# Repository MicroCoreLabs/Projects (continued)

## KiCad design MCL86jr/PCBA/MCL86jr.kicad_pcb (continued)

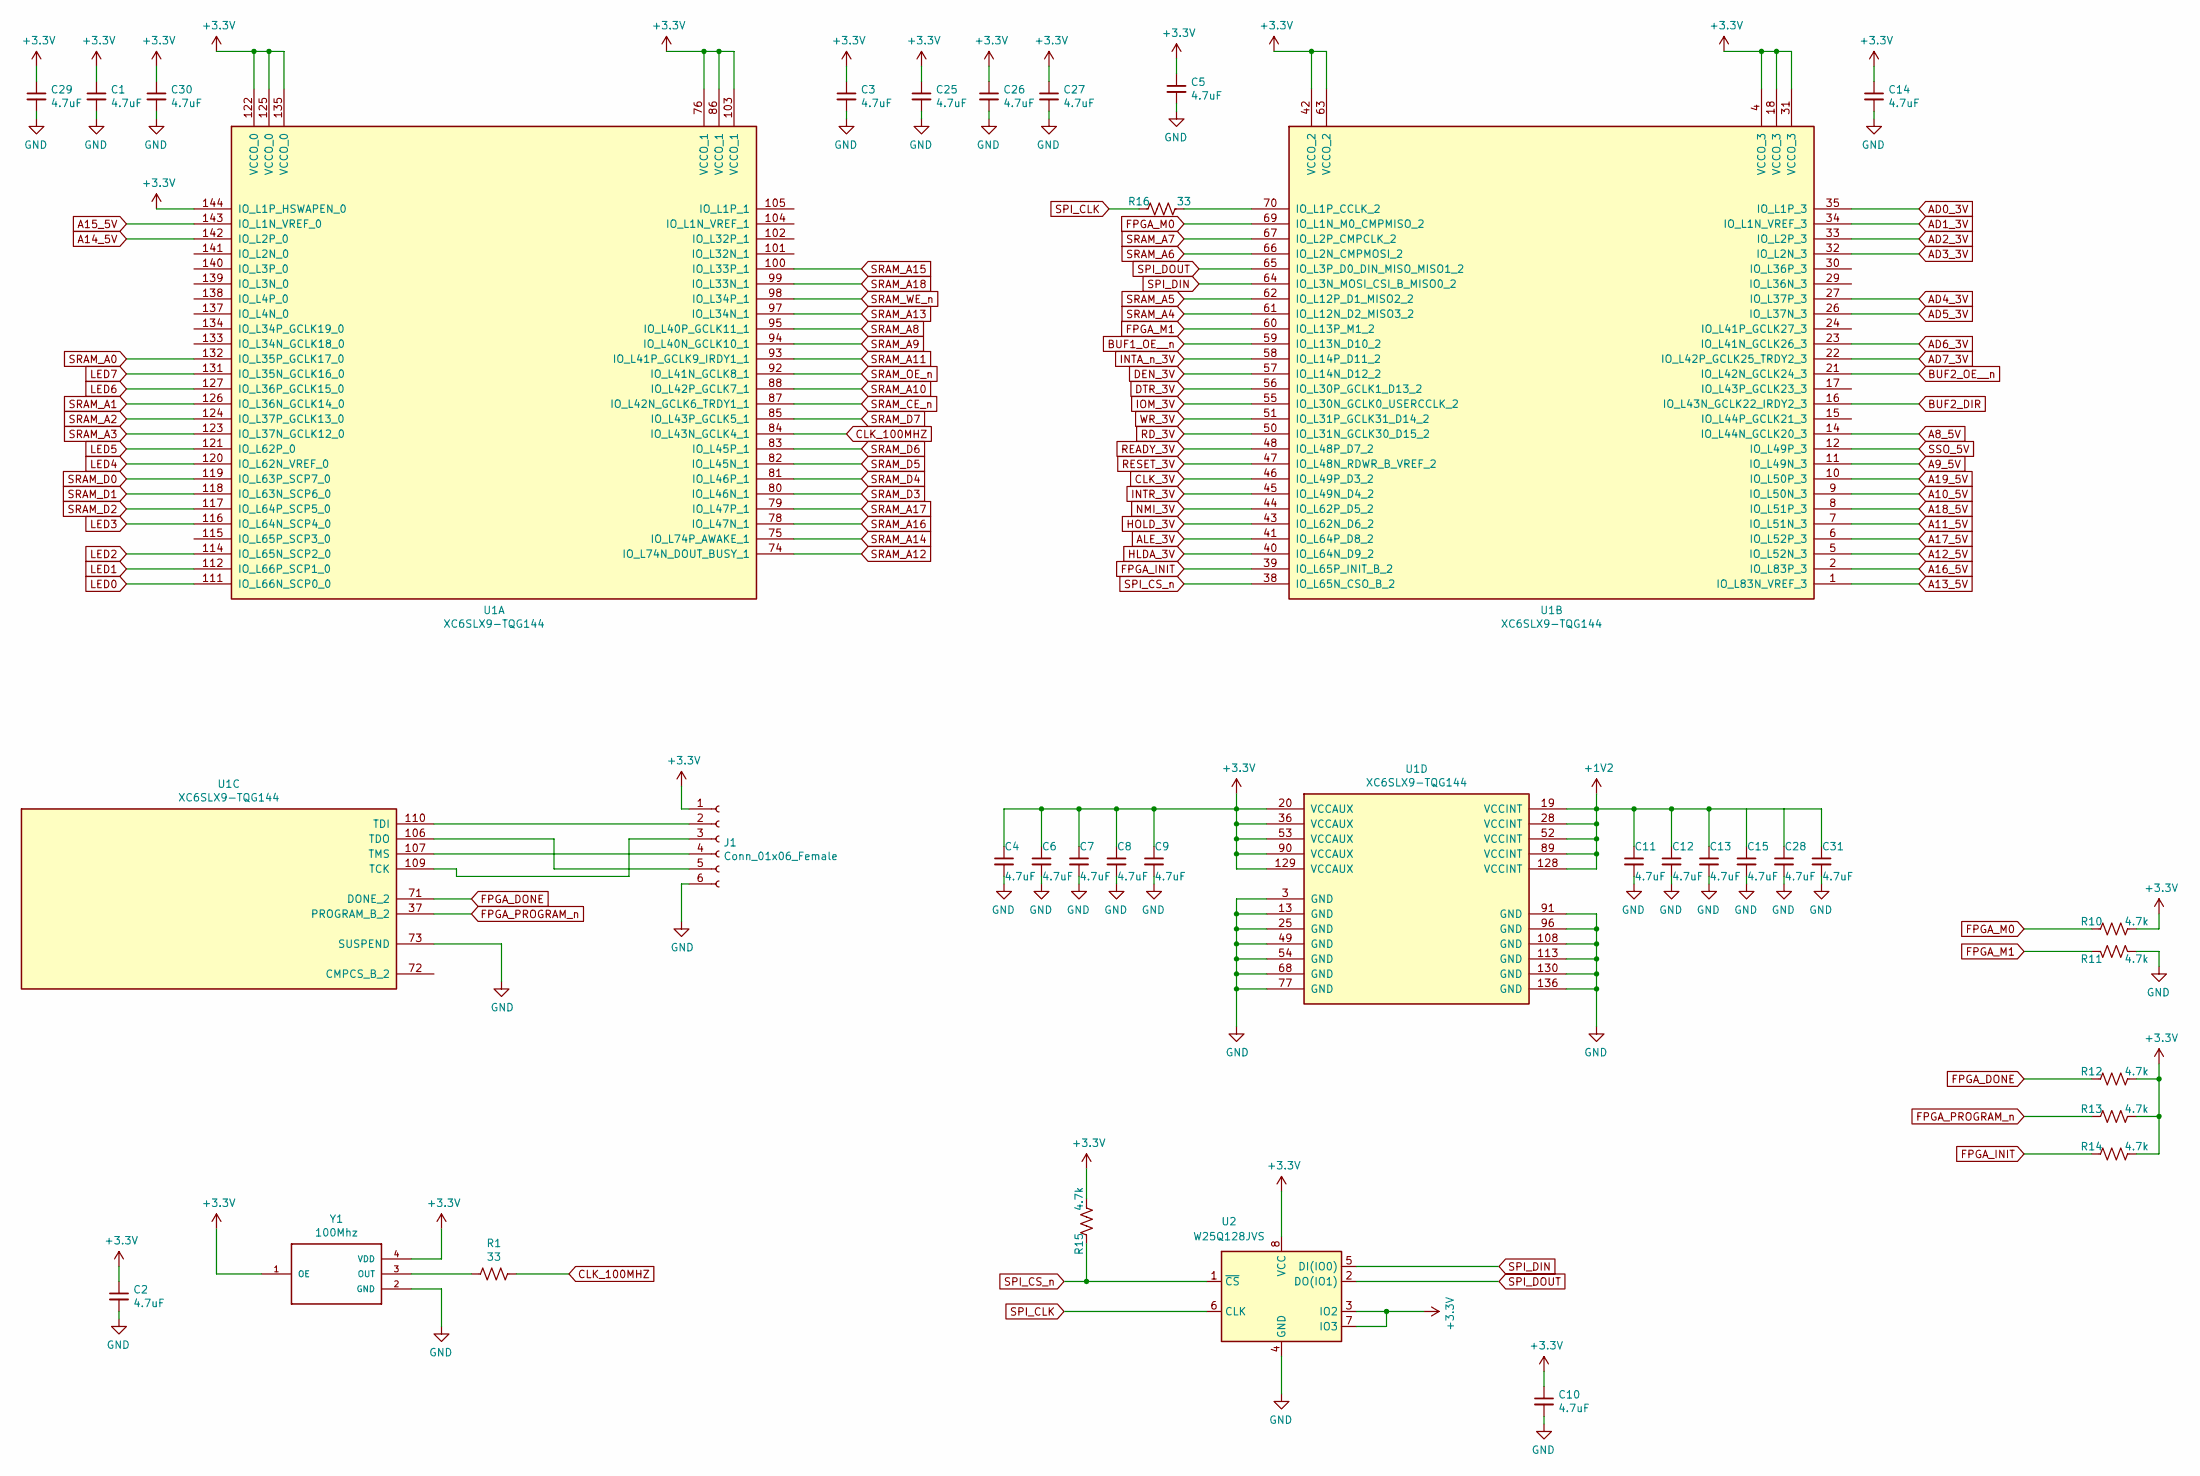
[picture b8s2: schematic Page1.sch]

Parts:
C1, C2, C3, C4, C5, C6, C7, C8, C9, C10, C11, C12, C13, C14, C15, C25, C26, C27, C28, C29, C30, C31: 4.7uF; C_0402_1005Metric
J1: Conn_01x06_Female; PinHeader_1x06_P2.54mm_Vertical
R1, R16: 33; R_0402_1005Metric
R10, R11, R12, R13, R14, R15: 4.7k; R_0402_1005Metric
U1: XC6SLX9-TQG144; TQFP-144_20x20mm_P0.5mm
U2: W25Q128JVS; SOIC-8_5.23x5.23mm_P1.27mm
Y1: 100Mhz; OSC_SIT8008BI-13-33E-33.333330E

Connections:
+1V2: C11.1, C12.1, C13.1, C15.1, C28.1, C31.1, U1.19 (VCCINT), U1.28 (VCCINT), U1.52 (VCCINT), U1.89 (VCCINT), U1.128 (VCCINT); also elsewhere on the board
+3V3: C1.1, C2.1, C3.1, C4.1, C5.1, C6.1, C7.1, C8.1, C9.1, C10.1, C14.1, C25.1, C26.1, C27.1, C29.1, C30.1, J1.1, R10.1, R12.1, R13.1, R14.1, R15.1, U1.4 (VCCO_3), U1.18 (VCCO_3), U1.20 (VCCAUX), U1.31 (VCCO_3), U1.36 (VCCAUX), U1.42 (VCCO_2), U1.53 (VCCAUX), U1.63 (VCCO_2), U1.76 (VCCO_1), U1.86 (VCCO_1), U1.90 (VCCAUX), U1.103 (VCCO_1), U1.122 (VCCO_0), U1.125 (VCCO_0), U1.129 (VCCAUX), U1.135 (VCCO_0), U1.144 (IO_L1P_HSWAPEN_0), U2.3 (IO2), U2.7 (IO3), U2.8 (VCC), Y1.1 (OE), Y1.4 (VDD); also elsewhere on the board
A8_5V: U1.14 (IO_L44N_GCLK20_3); also elsewhere on the board
A9_5V: U1.11 (IO_L49N_3); also elsewhere on the board
A10_5V: U1.9 (IO_L50N_3); also elsewhere on the board
A11_5V: U1.7 (IO_L51N_3); also elsewhere on the board
A12_5V: U1.5 (IO_L52N_3); also elsewhere on the board
A13_5V: U1.1 (IO_L83N_VREF_3); also elsewhere on the board
A14_5V: U1.142 (IO_L2P_0); also elsewhere on the board
A15_5V: U1.143 (IO_L1N_VREF_0); also elsewhere on the board
A16_5V: U1.2 (IO_L83P_3); also elsewhere on the board
A17_5V: U1.6 (IO_L52P_3); also elsewhere on the board
A18_5V: U1.8 (IO_L51P_3); also elsewhere on the board
A19_5V: U1.10 (IO_L50P_3); also elsewhere on the board
AD0_3V: U1.35 (IO_L1P_3); also elsewhere on the board
AD1_3V: U1.34 (IO_L1N_VREF_3); also elsewhere on the board
AD2_3V: U1.33 (IO_L2P_3); also elsewhere on the board
AD3_3V: U1.32 (IO_L2N_3); also elsewhere on the board
AD4_3V: U1.27 (IO_L37P_3); also elsewhere on the board
AD5_3V: U1.26 (IO_L37N_3); also elsewhere on the board
AD6_3V: U1.23 (IO_L41N_GCLK26_3); also elsewhere on the board
AD7_3V: U1.22 (IO_L42P_GCLK25_TRDY2_3); also elsewhere on the board
ALE_3V: U1.41 (IO_L64P_D8_2); also elsewhere on the board
BUF1_OE__n: U1.59 (IO_L13N_D10_2); also elsewhere on the board
BUF2_DIR: U1.16 (IO_L43N_GCLK22_IRDY2_3); also elsewhere on the board
BUF2_OE__n: U1.21 (IO_L42N_GCLK24_3); also elsewhere on the board
CLK_3V: U1.46 (IO_L49P_D3_2); also elsewhere on the board
CLK_100MHZ: R1.1, U1.84 (IO_L43N_GCLK4_1)
DEN_3V: U1.57 (IO_L14N_D12_2); also elsewhere on the board
DTR_3V: U1.56 (IO_L30P_GCLK1_D13_2); also elsewhere on the board
FPGA_DONE: R12.2, U1.71 (DONE_2)
FPGA_INIT: R14.2, U1.39 (IO_L65P_INIT_B_2)
FPGA_M0: R10.2, U1.69 (IO_L1N_M0_CMPMISO_2)
FPGA_M1: R11.2, U1.60 (IO_L13P_M1_2)
FPGA_PROGRAM_n: R13.2, U1.37 (PROGRAM_B_2)
GND: C1.2, C2.2, C3.2, C4.2, C5.2, C6.2, C7.2, C8.2, C9.2, C10.2, C11.2, C12.2, C13.2, C14.2, C15.2, C25.2, C26.2, C27.2, C28.2, C29.2, C30.2, C31.2, J1.6, R11.1, U1.3 (GND), U1.13 (GND), U1.25 (GND), U1.49 (GND), U1.54 (GND), U1.68 (GND), U1.73 (SUSPEND), U1.77 (GND), U1.91 (GND), U1.96 (GND), U1.108 (GND), U1.113 (GND), U1.130 (GND), U1.136 (GND), U2.4 (GND), Y1.2 (GND); also elsewhere on the board
HLDA_3V: U1.40 (IO_L64N_D9_2); also elsewhere on the board
HOLD_3V: U1.43 (IO_L62N_D6_2); also elsewhere on the board
INTA_n_3V: U1.58 (IO_L14P_D11_2); also elsewhere on the board
INTR_3V: U1.45 (IO_L49N_D4_2); also elsewhere on the board
IOM_3V: U1.55 (IO_L30N_GCLK0_USERCCLK_2); also elsewhere on the board
LED0: U1.111 (IO_L66N_SCP0_0); also elsewhere on the board
LED1: U1.112 (IO_L66P_SCP1_0); also elsewhere on the board
LED2: U1.114 (IO_L65N_SCP2_0); also elsewhere on the board
LED3: U1.116 (IO_L64N_SCP4_0); also elsewhere on the board
LED4: U1.120 (IO_L62N_VREF_0); also elsewhere on the board
LED5: U1.121 (IO_L62P_0); also elsewhere on the board
LED6: U1.127 (IO_L36P_GCLK15_0); also elsewhere on the board
LED7: U1.131 (IO_L35N_GCLK16_0); also elsewhere on the board
NMI_3V: U1.44 (IO_L62P_D5_2); also elsewhere on the board
unnamed: J1.2, U1.110 (TDI)
unnamed: J1.3, U1.109 (TCK)
unnamed: J1.4, U1.107 (TMS)
unnamed: J1.5, U1.106 (TDO)
unnamed: R1.2, Y1.3 (OUT)
unnamed: R16.1, U1.70 (IO_L1P_CCLK_2)
RD_3V: U1.50 (IO_L31N_GCLK30_D15_2); also elsewhere on the board
READY_3V: U1.48 (IO_L48P_D7_2); also elsewhere on the board
RESET_3V: U1.47 (IO_L48N_RDWR_B_VREF_2); also elsewhere on the board
SPI_CLK: R16.2, U2.6 (CLK)
SPI_CS_n: R15.2, U1.38 (IO_L65N_CSO_B_2), U2.1 (~CS)
SPI_DIN: U1.64 (IO_L3N_MOSI_CSI_B_MISO0_2), U2.5 (DI(IO0))
SPI_DOUT: U1.65 (IO_L3P_D0_DIN_MISO_MISO1_2), U2.2 (DO(IO1))
SRAM_A0: U1.132 (IO_L35P_GCLK17_0); also elsewhere on the board
SRAM_A1: U1.126 (IO_L36N_GCLK14_0); also elsewhere on the board
SRAM_A2: U1.124 (IO_L37P_GCLK13_0); also elsewhere on the board
SRAM_A3: U1.123 (IO_L37N_GCLK12_0); also elsewhere on the board
SRAM_A4: U1.61 (IO_L12N_D2_MISO3_2); also elsewhere on the board
SRAM_A5: U1.62 (IO_L12P_D1_MISO2_2); also elsewhere on the board
SRAM_A6: U1.66 (IO_L2N_CMPMOSI_2); also elsewhere on the board
SRAM_A7: U1.67 (IO_L2P_CMPCLK_2); also elsewhere on the board
SRAM_A8: U1.95 (IO_L40P_GCLK11_1); also elsewhere on the board
SRAM_A9: U1.94 (IO_L40N_GCLK10_1); also elsewhere on the board
SRAM_A10: U1.88 (IO_L42P_GCLK7_1); also elsewhere on the board
SRAM_A11: U1.93 (IO_L41P_GCLK9_IRDY1_1); also elsewhere on the board
SRAM_A12: U1.74 (IO_L74N_DOUT_BUSY_1); also elsewhere on the board
SRAM_A13: U1.97 (IO_L34N_1); also elsewhere on the board
SRAM_A14: U1.75 (IO_L74P_AWAKE_1); also elsewhere on the board
SRAM_A15: U1.100 (IO_L33P_1); also elsewhere on the board
SRAM_A16: U1.78 (IO_L47N_1); also elsewhere on the board
SRAM_A17: U1.79 (IO_L47P_1); also elsewhere on the board
SRAM_A18: U1.99 (IO_L33N_1); also elsewhere on the board
SRAM_CE_n: U1.87 (IO_L42N_GCLK6_TRDY1_1); also elsewhere on the board
SRAM_D0: U1.119 (IO_L63P_SCP7_0); also elsewhere on the board
SRAM_D1: U1.118 (IO_L63N_SCP6_0); also elsewhere on the board
SRAM_D2: U1.117 (IO_L64P_SCP5_0); also elsewhere on the board
SRAM_D3: U1.80 (IO_L46N_1); also elsewhere on the board
SRAM_D4: U1.81 (IO_L46P_1); also elsewhere on the board
SRAM_D5: U1.82 (IO_L45N_1); also elsewhere on the board
SRAM_D6: U1.83 (IO_L45P_1); also elsewhere on the board
SRAM_D7: U1.85 (IO_L43P_GCLK5_1); also elsewhere on the board
SRAM_OE_n: U1.92 (IO_L41N_GCLK8_1); also elsewhere on the board
SRAM_WE_n: U1.98 (IO_L34P_1); also elsewhere on the board
SSO_5V: U1.12 (IO_L49P_3); also elsewhere on the board
WR_3V: U1.51 (IO_L31P_GCLK31_D14_2); also elsewhere on the board

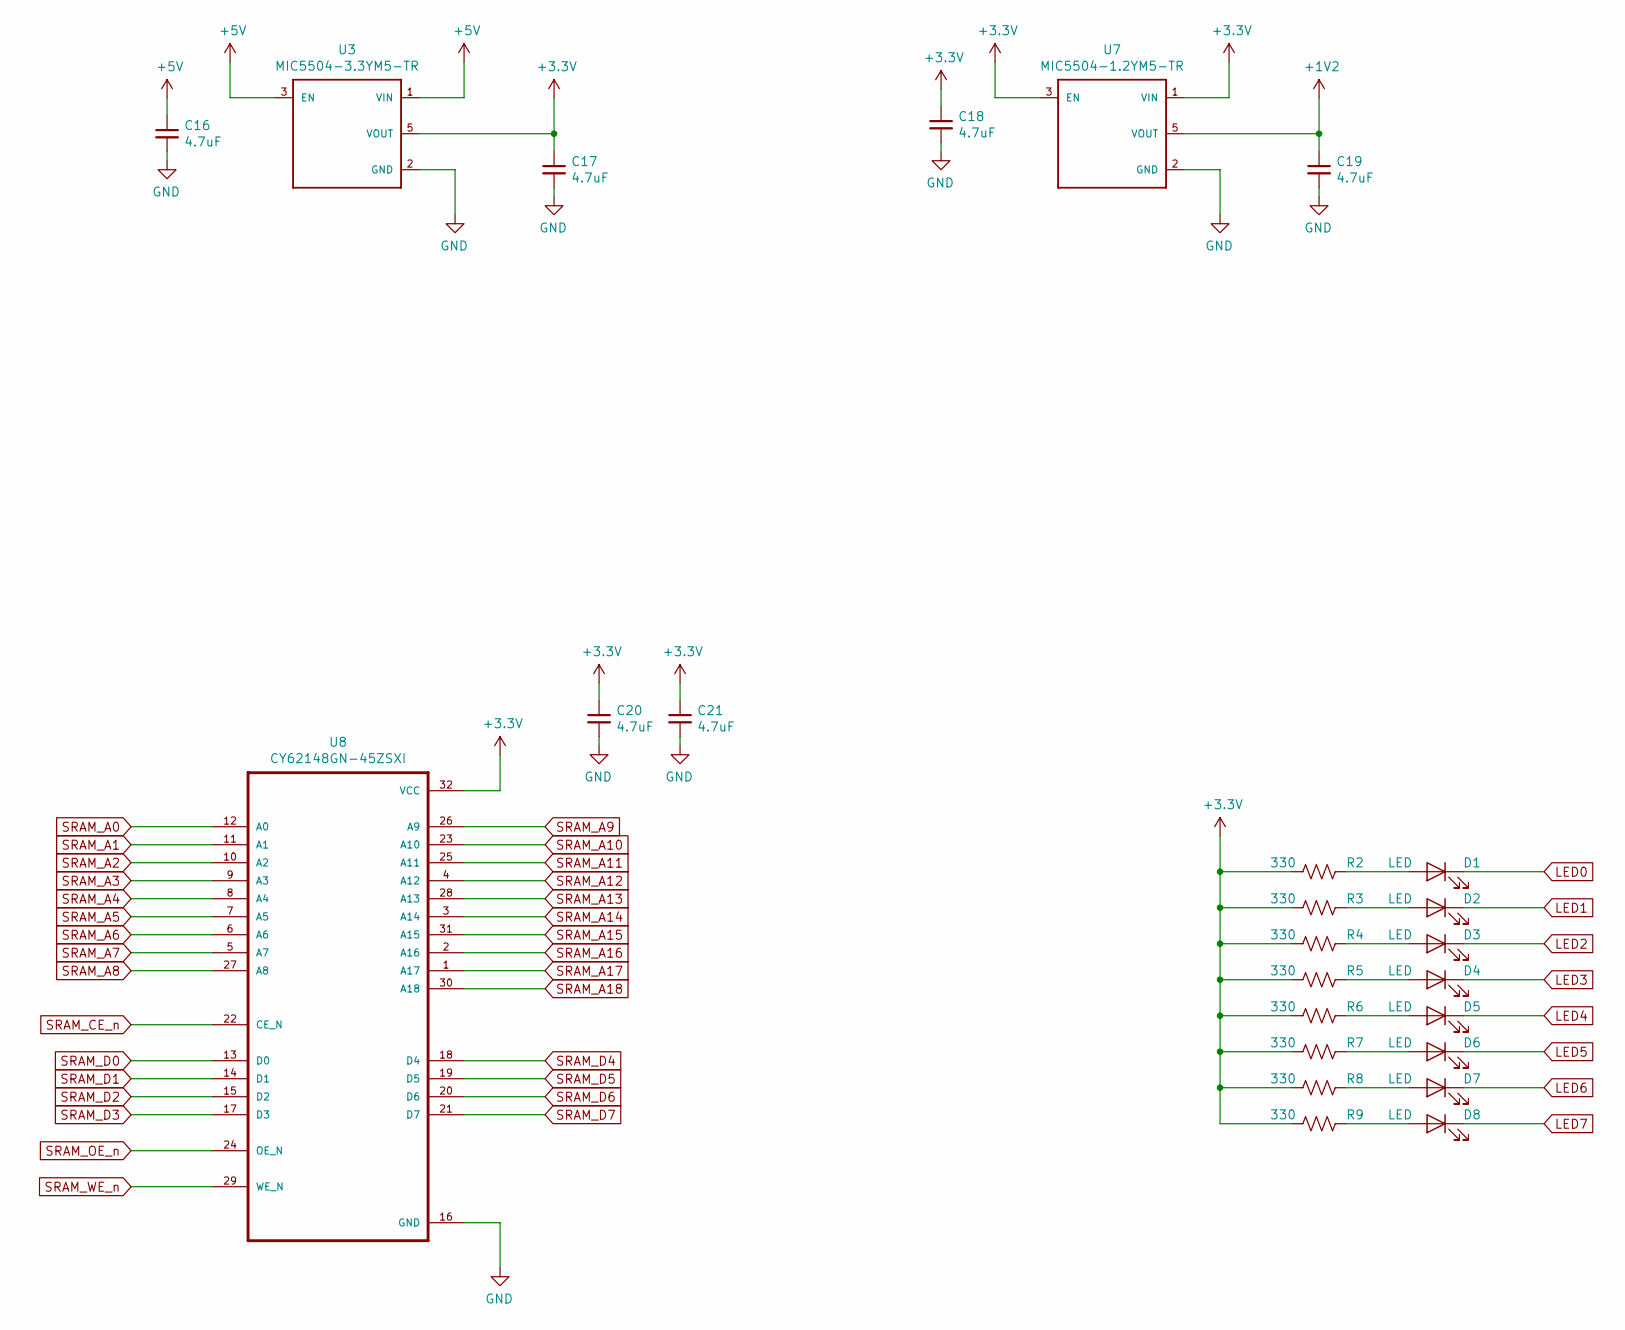
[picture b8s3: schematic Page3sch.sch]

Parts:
C16, C17, C18, C19, C20, C21: 4.7uF; C_0402_1005Metric
D1, D2, D3, D4, D5, D6, D7, D8: LED; LED_0402_1005Metric
R2, R3, R4, R5, R6, R7, R8, R9: 330; R_0402_1005Metric
U3: MIC5504-3.3YM5-TR; SOT23-5P95_280X145XL45X37N
U7: MIC5504-1.2YM5-TR; SOT23-5P95_280X145XL45X37N
U8: CY62148GN-45ZSXI; SOIC127P1176X120-32N

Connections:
+1V2: C19.1, U7.5 (VOUT); also elsewhere on the board
+3V3: C17.1, C18.1, C20.1, C21.1, R2.2, R3.2, R4.2, R5.2, R6.2, R7.2, R8.2, R9.2, U3.5 (VOUT), U7.1 (VIN), U7.3 (EN), U8.32 (VCC); also elsewhere on the board
+5V: C16.1, U3.1 (VIN), U3.3 (EN); also elsewhere on the board
GND: C16.2, C17.2, C18.2, C19.2, C20.2, C21.2, U3.2 (GND), U7.2 (GND), U8.16 (GND); also elsewhere on the board
LED0: D1.1 (K); also elsewhere on the board
LED1: D2.1 (K); also elsewhere on the board
LED2: D3.1 (K); also elsewhere on the board
LED3: D4.1 (K); also elsewhere on the board
LED4: D5.1 (K); also elsewhere on the board
LED5: D6.1 (K); also elsewhere on the board
LED6: D7.1 (K); also elsewhere on the board
LED7: D8.1 (K); also elsewhere on the board
unnamed: D1.2 (A), R2.1
unnamed: D2.2 (A), R3.1
unnamed: D3.2 (A), R4.1
unnamed: D4.2 (A), R5.1
unnamed: D5.2 (A), R6.1
unnamed: D6.2 (A), R7.1
unnamed: D7.2 (A), R8.1
unnamed: D8.2 (A), R9.1
SRAM_A0: U8.12 (A0); also elsewhere on the board
SRAM_A1: U8.11 (A1); also elsewhere on the board
SRAM_A2: U8.10 (A2); also elsewhere on the board
SRAM_A3: U8.9 (A3); also elsewhere on the board
SRAM_A4: U8.8 (A4); also elsewhere on the board
SRAM_A5: U8.7 (A5); also elsewhere on the board
SRAM_A6: U8.6 (A6); also elsewhere on the board
SRAM_A7: U8.5 (A7); also elsewhere on the board
SRAM_A8: U8.27 (A8); also elsewhere on the board
SRAM_A9: U8.26 (A9); also elsewhere on the board
SRAM_A10: U8.23 (A10); also elsewhere on the board
SRAM_A11: U8.25 (A11); also elsewhere on the board
SRAM_A12: U8.4 (A12); also elsewhere on the board
SRAM_A13: U8.28 (A13); also elsewhere on the board
SRAM_A14: U8.3 (A14); also elsewhere on the board
SRAM_A15: U8.31 (A15); also elsewhere on the board
SRAM_A16: U8.2 (A16); also elsewhere on the board
SRAM_A17: U8.1 (A17); also elsewhere on the board
SRAM_A18: U8.30 (A18); also elsewhere on the board
SRAM_CE_n: U8.22 (CE_N); also elsewhere on the board
SRAM_D0: U8.13 (D0); also elsewhere on the board
SRAM_D1: U8.14 (D1); also elsewhere on the board
SRAM_D2: U8.15 (D2); also elsewhere on the board
SRAM_D3: U8.17 (D3); also elsewhere on the board
SRAM_D4: U8.18 (D4); also elsewhere on the board
SRAM_D5: U8.19 (D5); also elsewhere on the board
SRAM_D6: U8.20 (D6); also elsewhere on the board
SRAM_D7: U8.21 (D7); also elsewhere on the board
SRAM_OE_n: U8.24 (OE_N); also elsewhere on the board
SRAM_WE_n: U8.29 (WE_N); also elsewhere on the board

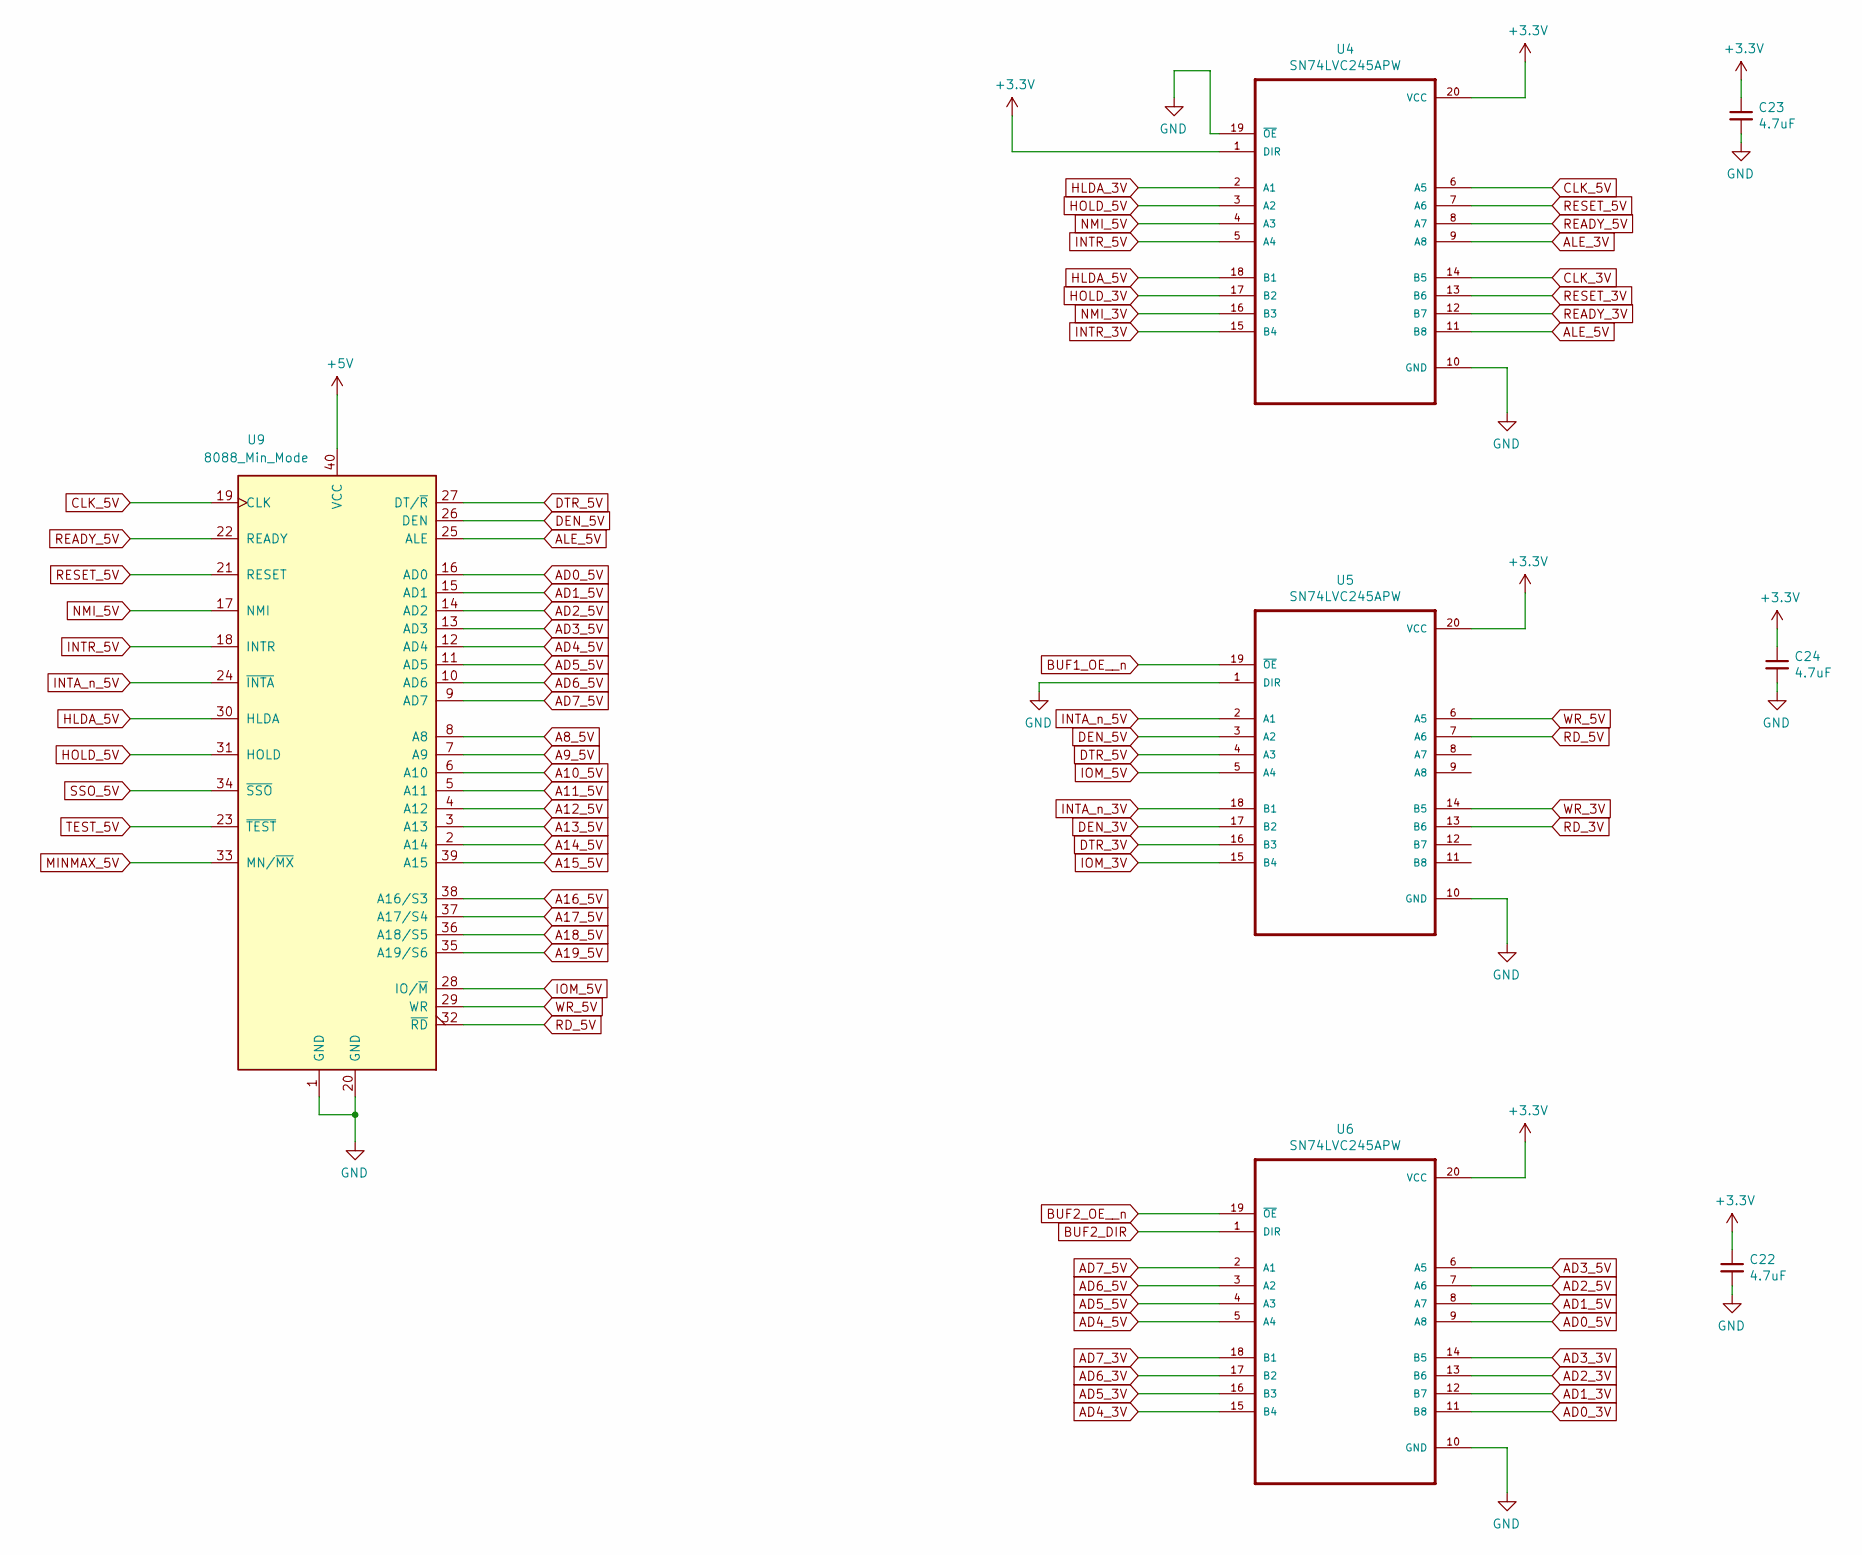
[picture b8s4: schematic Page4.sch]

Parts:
C22, C23, C24: 4.7uF; C_0402_1005Metric
U4, U5, U6: SN74LVC245APW; SOP65P640X120-20N
U9: 8088_Min_Mode; DIP-40_W15.24mm

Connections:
+3V3: C22.1, C23.1, C24.1, U4.1 (DIR), U4.20 (VCC), U5.20 (VCC), U6.20 (VCC); also elsewhere on the board
+5V: U9.40 (VCC); also elsewhere on the board
A8_5V: U9.8 (A8); also elsewhere on the board
A9_5V: U9.7 (A9); also elsewhere on the board
A10_5V: U9.6 (A10); also elsewhere on the board
A11_5V: U9.5 (A11); also elsewhere on the board
A12_5V: U9.4 (A12); also elsewhere on the board
A13_5V: U9.3 (A13); also elsewhere on the board
A14_5V: U9.2 (A14); also elsewhere on the board
A15_5V: U9.39 (A15); also elsewhere on the board
A16_5V: U9.38 (A16/S3); also elsewhere on the board
A17_5V: U9.37 (A17/S4); also elsewhere on the board
A18_5V: U9.36 (A18/S5); also elsewhere on the board
A19_5V: U9.35 (A19/S6); also elsewhere on the board
AD0_3V: U6.11 (B8); also elsewhere on the board
AD0_5V: U6.9 (A8), U9.16 (AD0)
AD1_3V: U6.12 (B7); also elsewhere on the board
AD1_5V: U6.8 (A7), U9.15 (AD1)
AD2_3V: U6.13 (B6); also elsewhere on the board
AD2_5V: U6.7 (A6), U9.14 (AD2)
AD3_3V: U6.14 (B5); also elsewhere on the board
AD3_5V: U6.6 (A5), U9.13 (AD3)
AD4_3V: U6.15 (B4); also elsewhere on the board
AD4_5V: U6.5 (A4), U9.12 (AD4)
AD5_3V: U6.16 (B3); also elsewhere on the board
AD5_5V: U6.4 (A3), U9.11 (AD5)
AD6_3V: U6.17 (B2); also elsewhere on the board
AD6_5V: U6.3 (A2), U9.10 (AD6)
AD7_3V: U6.18 (B1); also elsewhere on the board
AD7_5V: U6.2 (A1), U9.9 (AD7)
ALE_3V: U4.9 (A8); also elsewhere on the board
ALE_5V: U4.11 (B8), U9.25 (ALE)
BUF1_OE__n: U5.19 (~OE~); also elsewhere on the board
BUF2_DIR: U6.1 (DIR); also elsewhere on the board
BUF2_OE__n: U6.19 (~OE~); also elsewhere on the board
CLK_3V: U4.14 (B5); also elsewhere on the board
CLK_5V: U4.6 (A5), U9.19 (CLK)
DEN_3V: U5.17 (B2); also elsewhere on the board
DEN_5V: U5.3 (A2), U9.26 (DEN)
DTR_3V: U5.16 (B3); also elsewhere on the board
DTR_5V: U5.4 (A3), U9.27 (DT/~R~)
GND: C22.2, C23.2, C24.2, U4.10 (GND), U4.19 (~OE~), U5.1 (DIR), U5.10 (GND), U6.10 (GND), U9.1 (GND), U9.20 (GND); also elsewhere on the board
HLDA_3V: U4.2 (A1); also elsewhere on the board
HLDA_5V: U4.18 (B1), U9.30 (HLDA)
HOLD_3V: U4.17 (B2); also elsewhere on the board
HOLD_5V: U4.3 (A2), U9.31 (HOLD)
INTA_n_3V: U5.18 (B1); also elsewhere on the board
INTA_n_5V: U5.2 (A1), U9.24 (~INTA~)
INTR_3V: U4.15 (B4); also elsewhere on the board
INTR_5V: U4.5 (A4), U9.18 (INTR)
IOM_3V: U5.15 (B4); also elsewhere on the board
IOM_5V: U5.5 (A4), U9.28 (IO/~M~)
NMI_3V: U4.16 (B3); also elsewhere on the board
NMI_5V: U4.4 (A3), U9.17 (NMI)
RD_3V: U5.13 (B6); also elsewhere on the board
RD_5V: U5.7 (A6), U9.32 (~RD~)
READY_3V: U4.12 (B7); also elsewhere on the board
READY_5V: U4.8 (A7), U9.22 (READY)
RESET_3V: U4.13 (B6); also elsewhere on the board
RESET_5V: U4.7 (A6), U9.21 (RESET)
SSO_5V: U9.34 (~SSO~); also elsewhere on the board
WR_3V: U5.14 (B5); also elsewhere on the board
WR_5V: U5.6 (A5), U9.29 (WR)

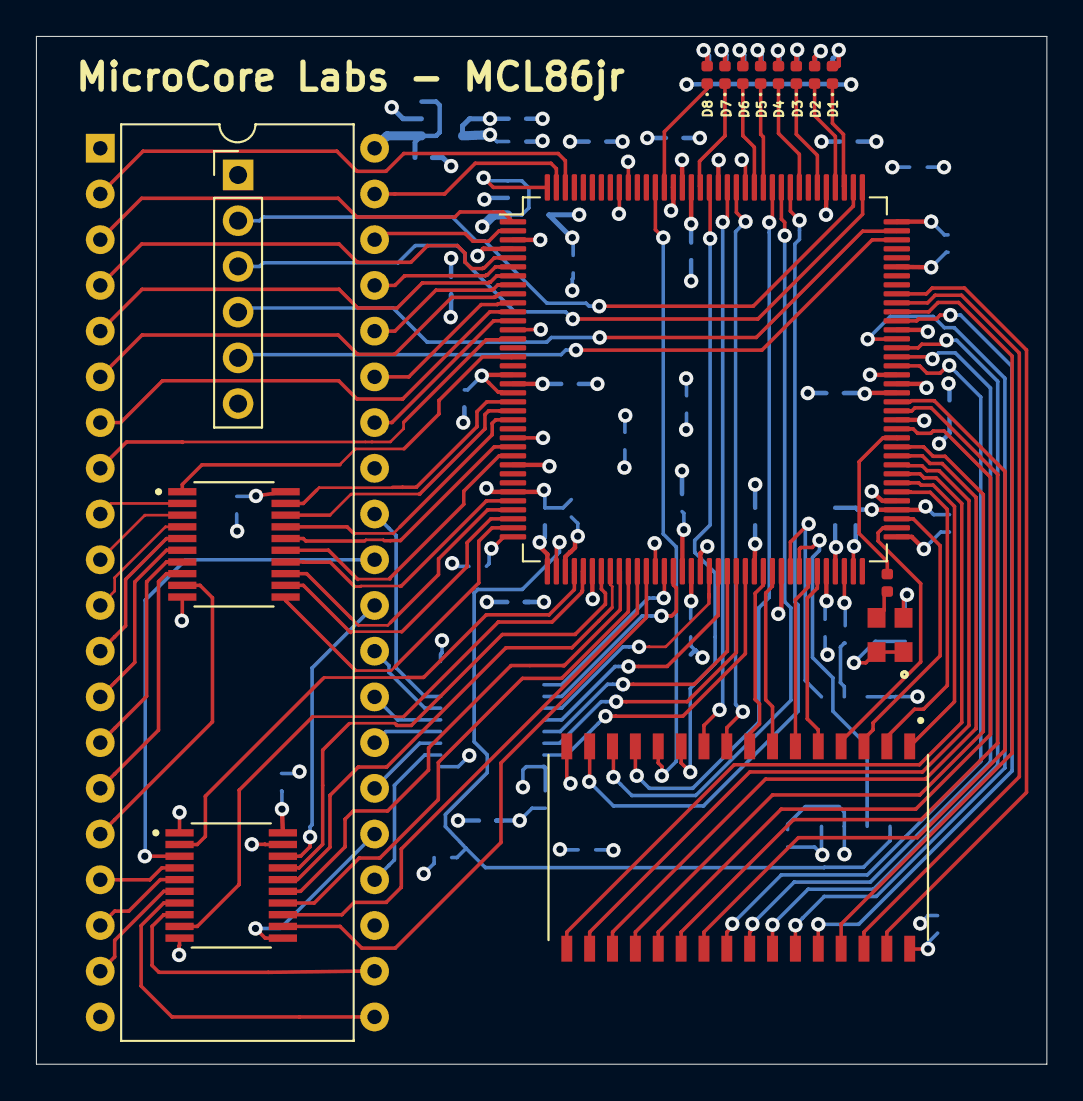
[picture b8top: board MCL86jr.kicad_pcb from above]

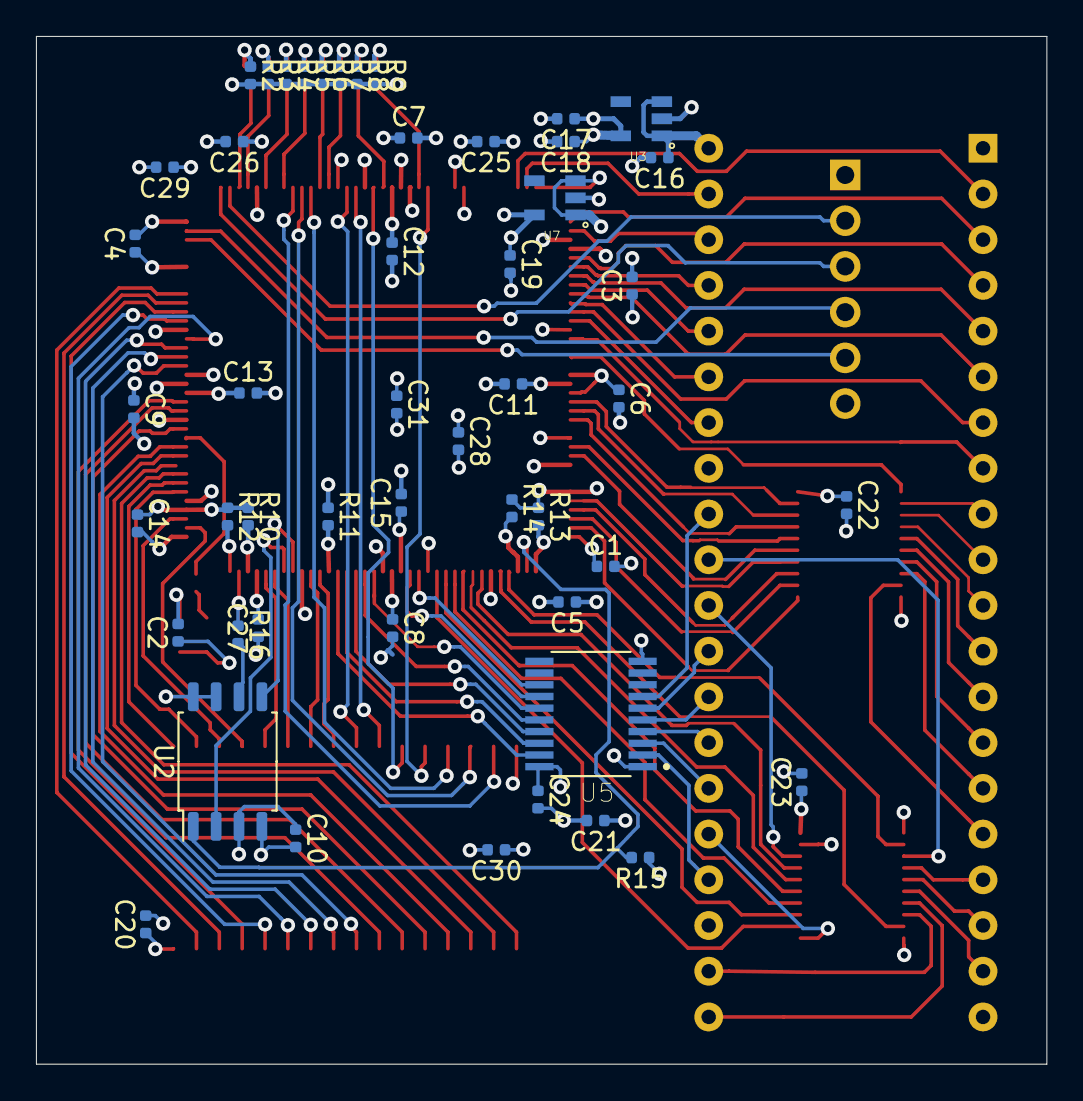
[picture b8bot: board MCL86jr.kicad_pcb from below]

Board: 4 copper layers, 56.1 x 57.1 mm, 66 parts (50 on the bottom side), 126 nets.

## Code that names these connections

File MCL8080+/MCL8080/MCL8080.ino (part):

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#include <stdint.h>


#define PIN_SPI_CS_n            PB3     
//#define PIN_SPI_CLK             7       
//#define PIN_SPI_MOSI            6       
//#define PIN_SPI_MISO            5       

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// USIWM0 = 3-wire mode
// USICS1 = External/Software clock source
// USICLK = Clock Strobe (links USITC to the shift register)
// USITC  = Toggle Clock Pin (PB2/USCK)
#define USI_FAST_CLK ((1 << USIWM0) | (1 << USICS0)| (1 << USICS1) | (1 << USICLK) | (1 << USITC))


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
void setup() {

    DDRB |= (1 << PB1) | (1 << PB2) | (1 << PB3); // DO, USCK, and your CS (PB3) as Output
    DDRB &= ~(1 << PB0);                          // DI as Input

    // Initialize USI for SPI Mode 1
    // USIWM0 = 3-wire mode
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    USICR = (1 << USIWM0) | (1 << USICS1) | (1 << USICS0);

    // Ensure Clock and CS_n starts LOW
    PORTB &= ~(1 << PB2);
    PORTB &= ~(1 << PIN_SPI_CS_n);

return;
}
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    temp8 = Send_SPI_Byte(local_data);    // Stream bytes with autoincrement address
  }

  else { PINB = (1<<PB3); // Toggle SPI_CS_n quickly
        Send_SPI_Byte(MEM_READ_BYTE);   
        Send_SPI_Byte(local_addr); 
        Send_SPI_Byte(local_addr>>8); 
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     Send_SPI_Byte(local_data);     // Stream bytes with autoincrement address
  }

  else { PINB = (1<<PB3); // Toggle SPI_CS_n quickly
         Send_SPI_Byte(MEM_WRITE_BYTE);   
         Send_SPI_Byte(local_addr); 
         Send_SPI_Byte(local_addr>>8); 
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}

else if (local_command==IO_READ_BYTE) {
  PINB = (1<<PB3); // Toggle SPI_CS_n quickly
  Send_SPI_Byte(IO_READ_BYTE);
  Send_SPI_Byte(local_addr); 
  temp8=Send_SPI_Byte(local_data);
}

else if (local_command==IO_WRITE_BYTE) {
  PINB = (1<<PB3); // Toggle SPI_CS_n quickly
  Send_SPI_Byte(IO_WRITE_BYTE); 
  Send_SPI_Byte(local_addr); 
  temp8=Send_SPI_Byte(local_data);
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
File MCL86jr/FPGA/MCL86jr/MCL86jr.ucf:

#Created by Constraints Editor (xc6slx9-tqg144-2) - 2016/06/18
NET "CORE_CLK" TNM_NET = "CORE_CLK";
TIMESPEC TS_CORE_CLK = PERIOD "CORE_CLK" 20 ns HIGH 50 %;


NET "CORE_CLK" IOSTANDARD = PCI33_3;
NET "A8" IOSTANDARD = PCI33_3;
NET "A9" IOSTANDARD = PCI33_3;
NET "A10" IOSTANDARD = PCI33_3;
NET "A11" IOSTANDARD = PCI33_3;
NET "A12" IOSTANDARD = PCI33_3;
NET "A13" IOSTANDARD = PCI33_3;
NET "A14" IOSTANDARD = PCI33_3;
NET "A15" IOSTANDARD = PCI33_3;
NET "A16" IOSTANDARD = PCI33_3;
NET "A17" IOSTANDARD = PCI33_3;
NET "A18" IOSTANDARD = PCI33_3;
NET "A19" IOSTANDARD = PCI33_3;
NET "AD0" IOSTANDARD = PCI33_3;
NET "AD1" IOSTANDARD = PCI33_3;
NET "AD2" IOSTANDARD = PCI33_3;
NET "AD3" IOSTANDARD = PCI33_3;
NET "AD4" IOSTANDARD = PCI33_3;
NET "AD5" IOSTANDARD = PCI33_3;
NET "AD6" IOSTANDARD = PCI33_3;
NET "AD7" IOSTANDARD = PCI33_3;
NET "CLK" IOSTANDARD = PCI33_3;
NET "INTR" IOSTANDARD = PCI33_3;
NET "NMI" IOSTANDARD = LVCMOS33;
NET "READY" IOSTANDARD = PCI33_3;
NET "RESET" IOSTANDARD = PCI33_3;
NET "ALE" IOSTANDARD = PCI33_3;
NET "INTA_n" IOSTANDARD = PCI33_3;
NET "RD_n" IOSTANDARD = PCI33_3;
NET "DEN" IOSTANDARD = PCI33_3;
NET "WR_n" IOSTANDARD = PCI33_3;
NET "DTR" IOSTANDARD = PCI33_3;
NET "IOM" IOSTANDARD = PCI33_3;

NET "SRAM_A[18]" IOSTANDARD = PCI33_3;
NET "SRAM_A[17]" IOSTANDARD = PCI33_3;
NET "SRAM_A[16]" IOSTANDARD = PCI33_3;
NET "SRAM_A[15]" IOSTANDARD = PCI33_3;
NET "SRAM_A[14]" IOSTANDARD = PCI33_3;
NET "SRAM_A[13]" IOSTANDARD = PCI33_3;
NET "SRAM_A[12]" IOSTANDARD = PCI33_3;
NET "SRAM_A[11]" IOSTANDARD = PCI33_3;
NET "SRAM_A[10]" IOSTANDARD = PCI33_3;
NET "SRAM_A[9]" IOSTANDARD = PCI33_3;
NET "SRAM_A[8]" IOSTANDARD = PCI33_3;
NET "SRAM_A[7]" IOSTANDARD = PCI33_3;
NET "SRAM_A[6]" IOSTANDARD = PCI33_3;
NET "SRAM_A[5]" IOSTANDARD = PCI33_3;
NET "SRAM_A[4]" IOSTANDARD = PCI33_3;
NET "SRAM_A[3]" IOSTANDARD = PCI33_3;
NET "SRAM_A[2]" IOSTANDARD = PCI33_3;
NET "SRAM_A[1]" IOSTANDARD = PCI33_3;
NET "SRAM_A[0]" IOSTANDARD = PCI33_3;
NET "SRAM_CE_n" IOSTANDARD = PCI33_3;
NET "SRAM_OE_n" IOSTANDARD = PCI33_3;
NET "SRAM_WE_n" IOSTANDARD = PCI33_3;
NET "SRAM_D[7]" IOSTANDARD = PCI33_3;
NET "SRAM_D[6]" IOSTANDARD = PCI33_3;
NET "SRAM_D[5]" IOSTANDARD = PCI33_3;
NET "SRAM_D[4]" IOSTANDARD = PCI33_3;
NET "SRAM_D[3]" IOSTANDARD = PCI33_3;
NET "SRAM_D[2]" IOSTANDARD = PCI33_3;
NET "SRAM_D[1]" IOSTANDARD = PCI33_3;
NET "SRAM_D[0]" IOSTANDARD = PCI33_3;

NET "LED[7]" IOSTANDARD = PCI33_3;
NET "LED[6]" IOSTANDARD = PCI33_3;
NET "LED[5]" IOSTANDARD = PCI33_3;
NET "LED[4]" IOSTANDARD = PCI33_3;
NET "LED[3]" IOSTANDARD = PCI33_3;
NET "LED[2]" IOSTANDARD = PCI33_3;
NET "LED[1]" IOSTANDARD = PCI33_3;
NET "LED[0]" IOSTANDARD = PCI33_3;

NET "BUF1_OE_n" IOSTANDARD = PCI33_3;
NET "BUF2_OE_n" IOSTANDARD = PCI33_3;
NET "BUF2_DIR" IOSTANDARD = PCI33_3;
NET "SSO_n" IOSTANDARD = PCI33_3;






NET "A8" LOC = P14;
NET "A9" LOC = P11;
NET "A10" LOC = P9;
NET "A11" LOC = P7;
NET "A12" LOC = P5;
NET "A13" LOC = P1;
NET "A14" LOC = P142;
NET "A15" LOC = P143;
NET "A16" LOC = P2;
NET "A17" LOC = P6;
NET "A18" LOC = P8;
NET "A19" LOC = P10;
NET "AD0" LOC = P35;
NET "AD1" LOC = P34;
NET "AD2" LOC = P33;
NET "AD3" LOC = P32;
NET "AD4" LOC = P27;
NET "AD5" LOC = P26;
NET "AD6" LOC = P23;
NET "AD7" LOC = P22;
NET "CLK" LOC = P46;
NET "INTR" LOC = P45;
NET "NMI" LOC = P44;
NET "READY" LOC = P48;
NET "RESET" LOC = P47;
NET "ALE" LOC = P41;
NET "INTA_n" LOC = P58;
NET "RD_n" LOC = P50;
NET "WR_n" LOC = P51;
NET "IOM" LOC = P55;
NET "DTR" LOC = P56;
NET "DEN" LOC = P57;

NET "SRAM_A[18]" LOC = P99;
NET "SRAM_A[17]" LOC = P79;
NET "SRAM_A[16]" LOC = P78;
NET "SRAM_A[15]" LOC = P100;
NET "SRAM_A[14]" LOC = P75;
NET "SRAM_A[13]" LOC = P97;
NET "SRAM_A[12]" LOC = P74;
NET "SRAM_A[11]" LOC = P93;
NET "SRAM_A[10]" LOC = P88;
NET "SRAM_A[9]" LOC = P94;
NET "SRAM_A[8]" LOC = P95;
NET "SRAM_A[7]" LOC = P67;
NET "SRAM_A[6]" LOC = P66;
NET "SRAM_A[5]" LOC = P62;
NET "SRAM_A[4]" LOC = P61;
NET "SRAM_A[3]" LOC = P123;
NET "SRAM_A[2]" LOC = P124;
NET "SRAM_A[1]" LOC = P126;
NET "SRAM_A[0]" LOC = P132;

NET "SRAM_CE_n" LOC = P87;
NET "SRAM_OE_n" LOC = P92;
NET "SRAM_WE_n" LOC = P98;

NET "SRAM_D[7]" LOC = P85;
NET "SRAM_D[6]" LOC = P83;
NET "SRAM_D[5]" LOC = P82;
NET "SRAM_D[4]" LOC = P81;
NET "SRAM_D[3]" LOC = P80;
NET "SRAM_D[2]" LOC = P117;
NET "SRAM_D[1]" LOC = P118;
NET "SRAM_D[0]" LOC = P119;

NET "LED[7]" LOC = P131;
NET "LED[6]" LOC = P127;
NET "LED[5]" LOC = P121;
NET "LED[4]" LOC = P120;
NET "LED[3]" LOC = P116;
NET "LED[2]" LOC = P114;
NET "LED[1]" LOC = P112;
NET "LED[0]" LOC = P111;


NET "CORE_CLK" LOC = P84;


NET "BUF1_OE_n" LOC = P59;
NET "BUF2_OE_n" LOC = P21;
NET "BUF2_DIR" LOC = P16;
NET "SSO_n" LOC = P12;


# PlanAhead Generated IO constraints 

NET "NMI" PULLDOWN;

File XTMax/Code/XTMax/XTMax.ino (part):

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#define PIN_IOWR_n          3
#define PIN_IORD_n          2
   
#define PIN_MUX_DATA_n      31     
#define PIN_DATA_OE_n       30     
#define PIN_MUX_ADDR_n      9
#define PIN_TRIG_OUT        35
 
#define PIN_ADDR19          27
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  pinMode(PIN_IOWR_n,         INPUT);
  pinMode(PIN_IORD_n,         INPUT);
 
  pinMode(PIN_MUX_DATA_n,     OUTPUT);   
  pinMode(PIN_DATA_OE_n,      OUTPUT);   
  pinMode(PIN_MUX_ADDR_n,     OUTPUT);
  pinMode(PIN_TRIG_OUT,       OUTPUT);
 
  pinMode(PIN_ADDR19,         INPUT);
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  digitalWriteFast(PIN_CHRDY_OE_n,   0x1);
  digitalWriteFast(PIN_CHRDY_OUT,    0x0);
 
  digitalWriteFast(PIN_DATA_OE_n,    0x1);
  digitalWriteFast(PIN_MUX_ADDR_n,   0x0);
  digitalWriteFast(PIN_MUX_DATA_n,   0x1);
  digitalWriteFast(PIN_TRIG_OUT,     0x1);
 

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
